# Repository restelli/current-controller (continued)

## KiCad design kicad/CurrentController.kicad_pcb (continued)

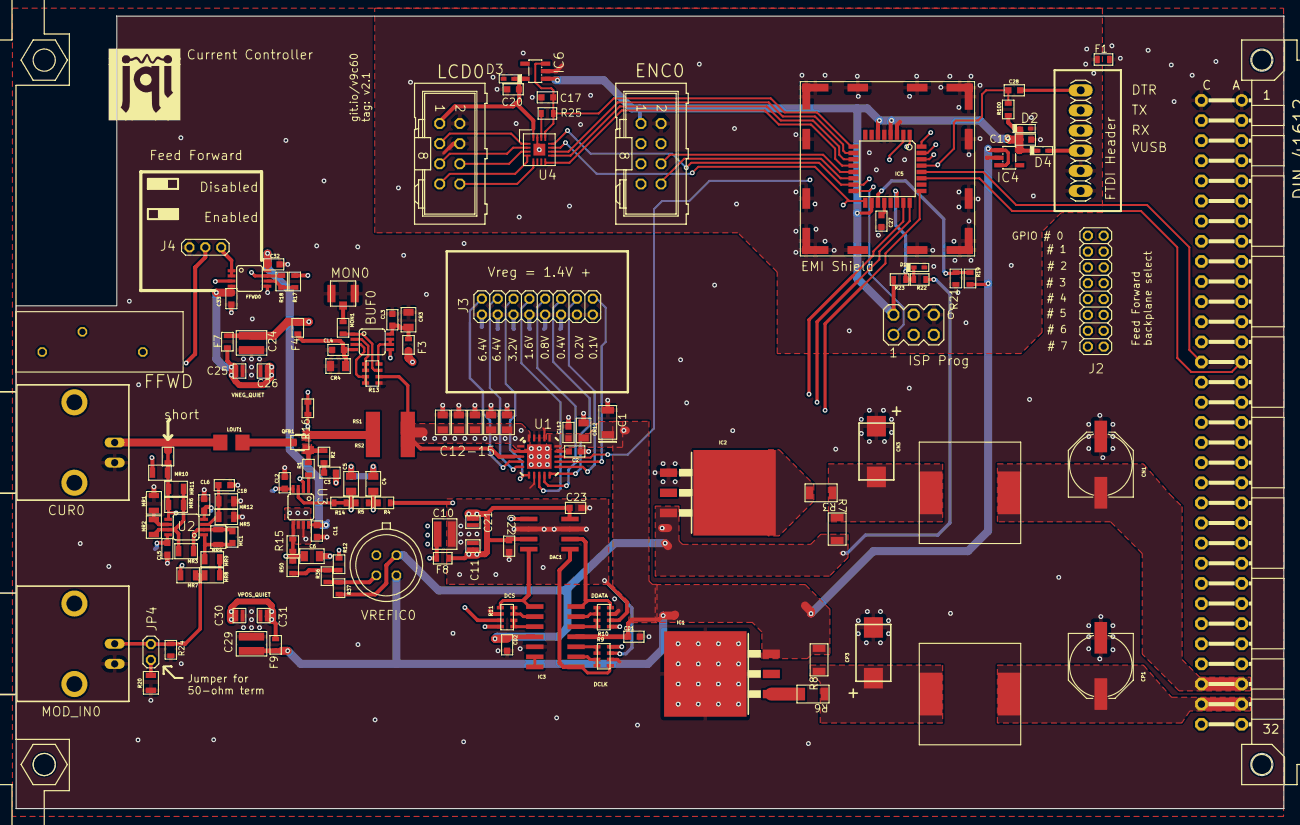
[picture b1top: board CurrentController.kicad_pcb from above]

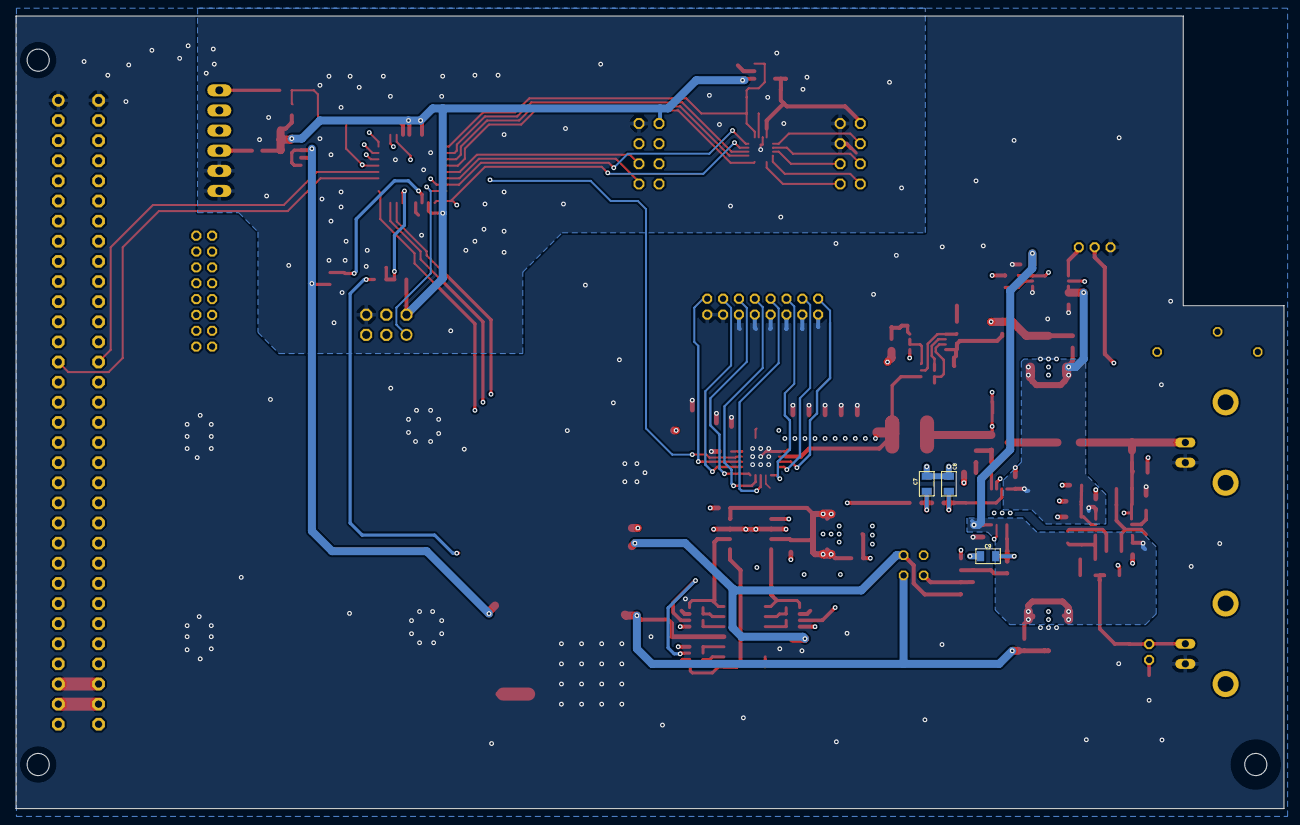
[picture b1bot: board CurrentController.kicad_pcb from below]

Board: 4 copper layers, 160.0 x 100.0 mm, 139 parts (3 on the bottom side), 112 nets.

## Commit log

2024-09-20 Eagle --> Kicad conversion in ./kicad New folder ./kicad created - Old Eagle project left untouched - Synchronization between schematic and layout attempted causing 22 nets to result unconnected - Pr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
